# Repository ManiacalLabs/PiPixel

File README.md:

If you require support, please post to the [Maniacal Labs Google Group](https://github.com/ManiacalLabs/PiPixel/blob/master/Usage.md#data-output-options).

# Maniacal Labs PiPixel

The PiPixel provides simplified hookup of digital LED strips to the Raspberry Pi family of single board computers. It uses the standard Pi "HAT" form-factor to provide two easy power input options, and data output of the SPI port as well as GPIO 18 and 13 (used for WS2812), along with built-in voltage level shifting to keep your LED strips happy being connected to the 3.3V Pi. No longer will you have a rats-nest of wires and power between your Pi and your LEDs. Slap on the PiPixel, connect power, connect LEDs, and go!

# What's In The Bag

Your PiPixel is a user assembled kit which only requires basic soldering skills and comes with the following components:

- PiPixel PCB
- Female 2x20 Header for connection to Pi
- 2.1 / 5.5 mm barrel jack for power input option #1
- 5mm pitch dual screw terminal for power input option #2
- 74AHCT125 Level Shifter
- 4 pin screw terminal for data/power output
- 2x3 pin header and jumper for data line selection

# Where To Get Optional Headers

We ship the PiPixel with a standard 2x20 Female header as that's what most users are likely to use. But it supports a few other options which we don't currently provide. See the list below for links of where to buy those, should you need them.

- [Extra Tall Female Header](https://www.sparkfun.com/products/14017)
- [Male Header](https://www.sparkfun.com/products/14275)
- [Stacking Header](https://www.adafruit.com/product/1979)
- [Ribbon Cable](https://www.sparkfun.com/products/13028)

# Assembly

Check out the full [Assembly doc](Assembly.md)

# Usage

For all the details on using your PiPixel, check out the [Usage doc](Usage.md)

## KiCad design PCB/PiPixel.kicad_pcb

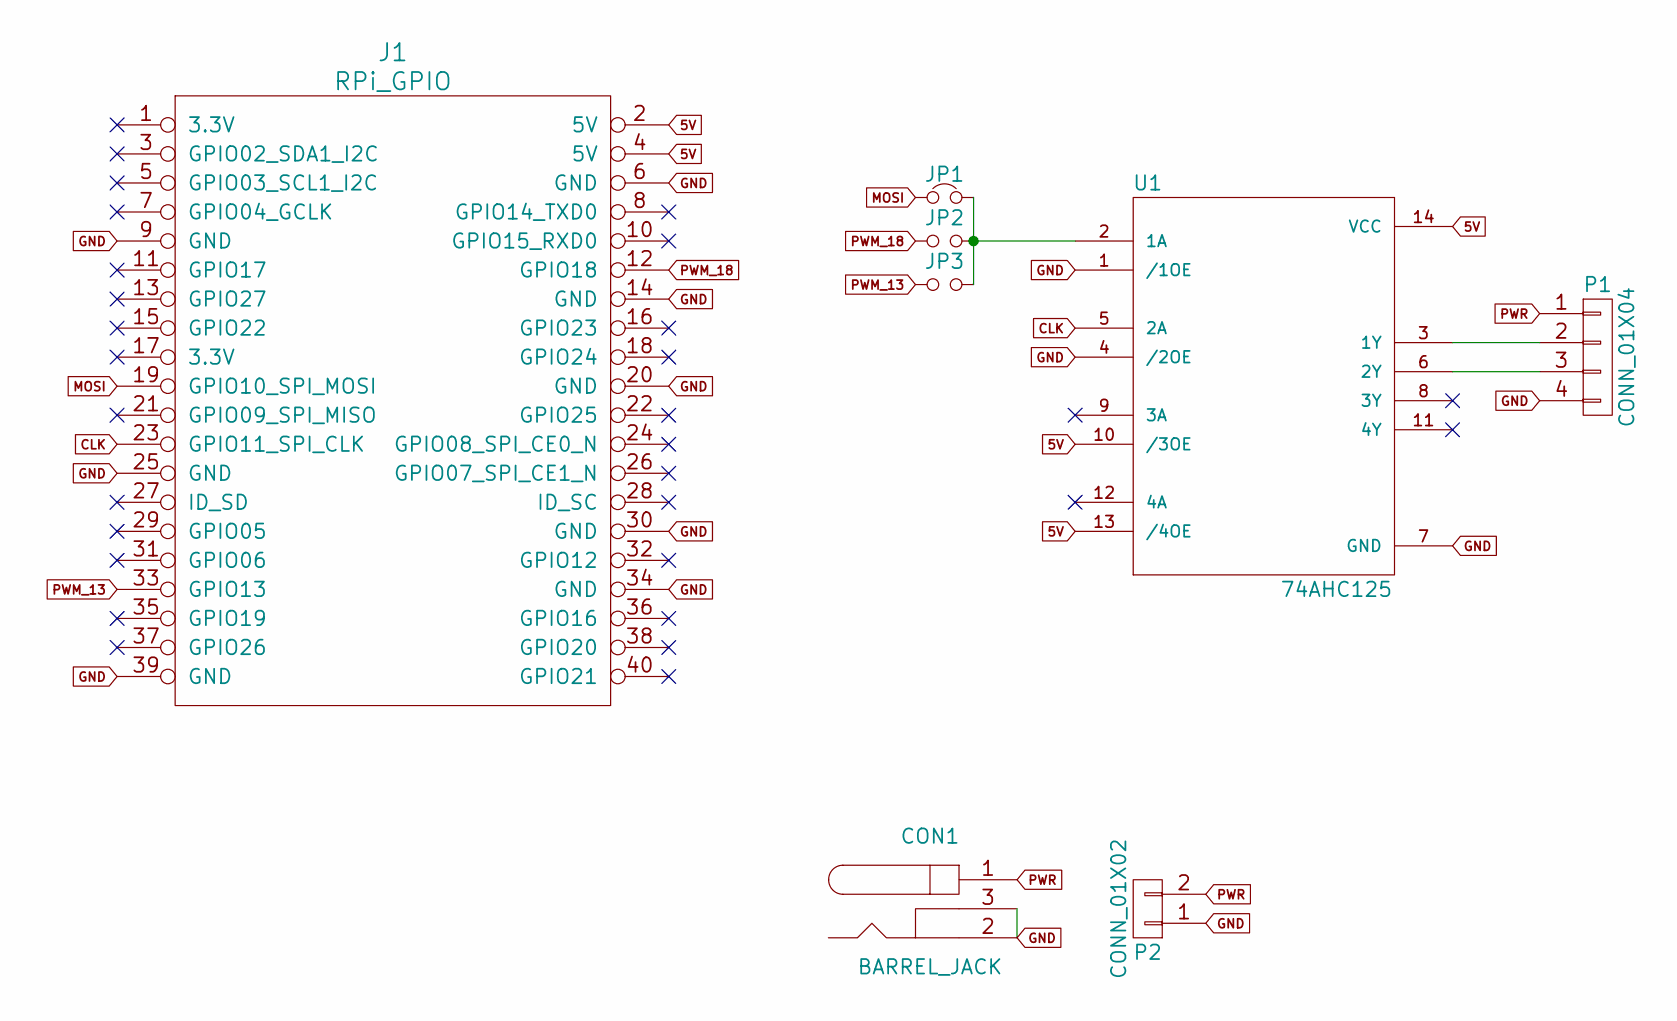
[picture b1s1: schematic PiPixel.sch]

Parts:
CON1: BARREL_JACK; ML_BARREL_JACK_ROUND_PADS_SHORT
J1: RPi_GPIO; Pin_Header_Straight_2x20
JP1: Jumper_NC_Small; Socket_Strip_Straight_1x02
JP2, JP3: Jumper_NO_Small; Socket_Strip_Straight_1x02
P1: CONN_01X04; mpt_0,5%2f4-2,54
P2: CONN_01X02; mkds_1,5-2
U1: 74AHC125; DIP-14_W7.62mm_LongPads

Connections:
5V: J1.2 (5V), J1.4 (5V), U1.10 (/3OE), U1.13 (/4OE), U1.14 (VCC)
CLK: J1.23 (GPIO11_SPI_CLK), U1.5 (2A)
GND: CON1.2, CON1.3, J1.6 (GND), J1.9 (GND), J1.14 (GND), J1.20 (GND), J1.25 (GND), J1.30 (GND), J1.34 (GND), J1.39 (GND), P1.4, P2.1, U1.1 (/1OE), U1.4 (/2OE), U1.7 (GND)
MOSI: J1.19 (GPIO10_SPI_MOSI), JP1.1
unnamed: JP1.2, JP2.2, JP3.2, U1.2 (1A)
unnamed: P1.2, U1.3 (1Y)
unnamed: P1.3, U1.6 (2Y)
PWM_13: J1.33 (GPIO13), JP3.1
PWM_18: J1.12 (GPIO18), JP2.1
PWR: CON1.1, P1.1, P2.2

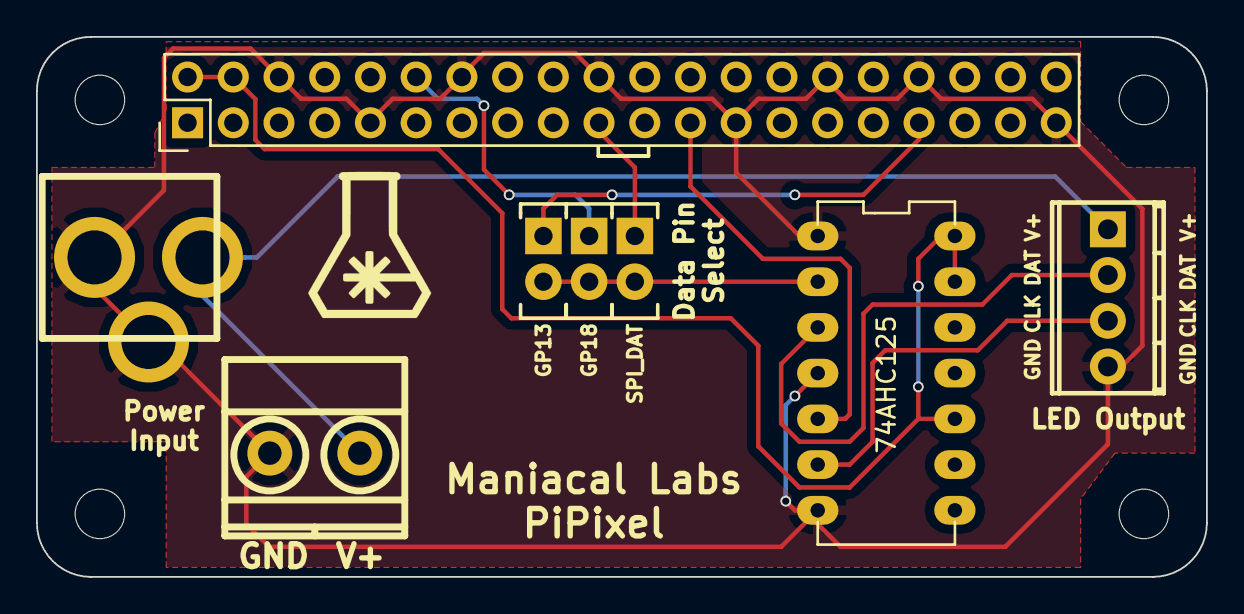
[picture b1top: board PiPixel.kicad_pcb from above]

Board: 2 copper layers, 65.0 x 30.0 mm, 8 parts (0 on the bottom side), 10 nets.

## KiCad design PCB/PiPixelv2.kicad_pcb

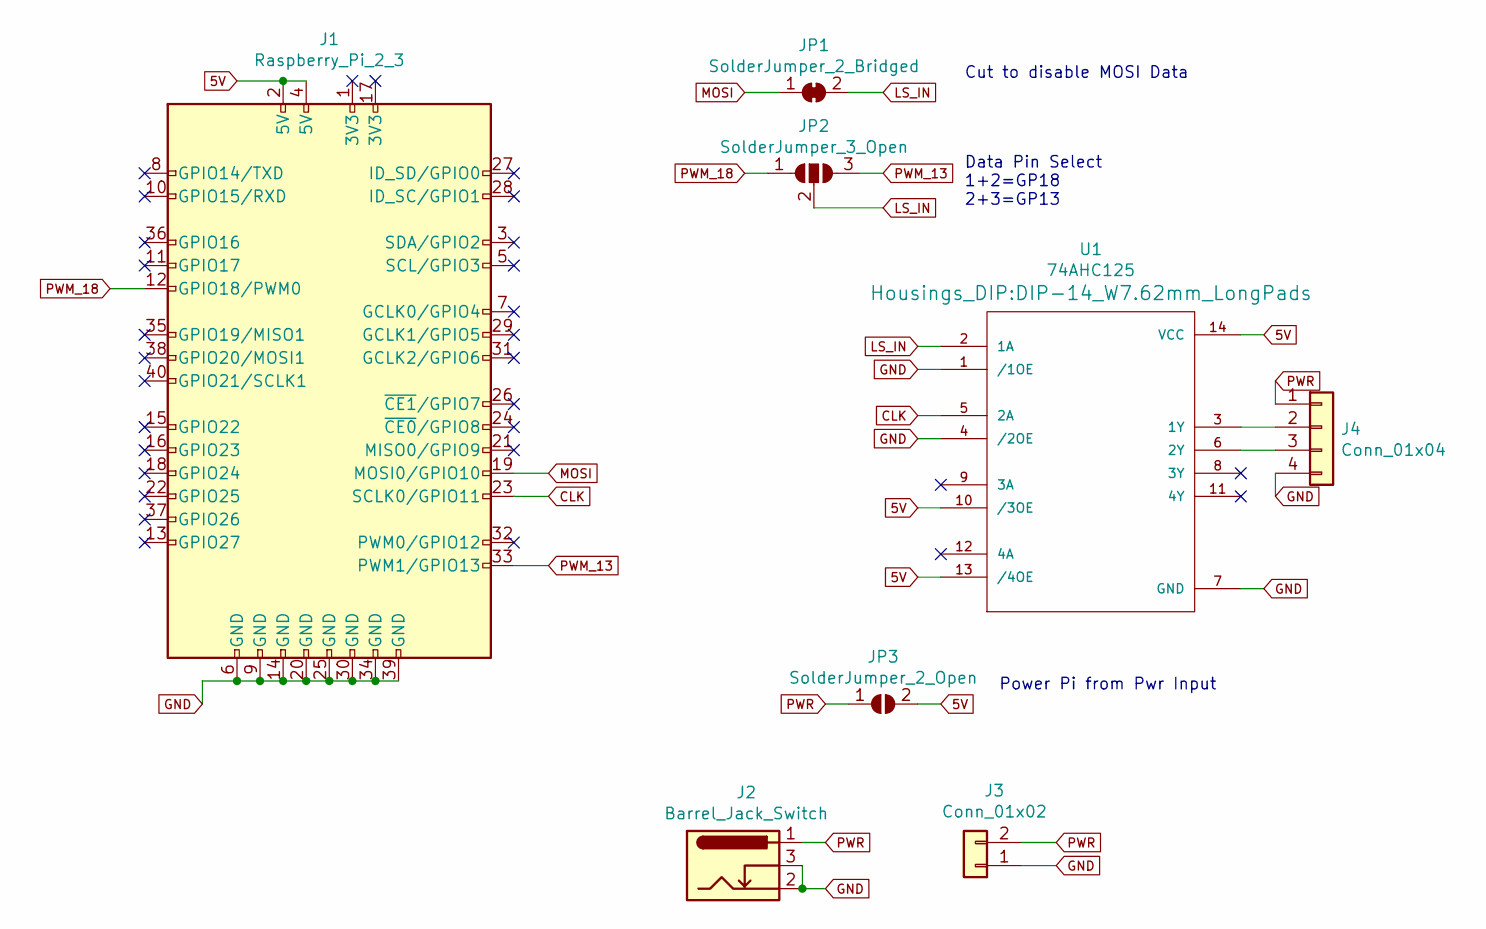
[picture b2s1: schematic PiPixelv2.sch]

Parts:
J1: Raspberry_Pi_2_3; Pin_Header_Straight_2x20_Pitch2.54mm
J2: Barrel_Jack_Switch; ML_BARREL_JACK_ROUND_PADS_SHORT
J3: Conn_01x02; mkds_1,5-2
J4: Conn_01x04; mpt_0,5%2f4-2,54
JP1: SolderJumper_2_Bridged; SolderJumper-2_P1.3mm_Bridged_Pad1.0x1.5mm
JP2: SolderJumper_3_Open; SolderJumper-3_P1.3mm_Open_Pad1.0x1.5mm_NumberLabels
JP3: SolderJumper_2_Open; SolderJumper-2_P1.3mm_Open_Pad1.0x1.5mm
U1: 74AHC125; DIP-14_W7.62mm_LongPads

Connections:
5V: J1.2 (5V), J1.4 (5V), JP3.2 (B), U1.10 (/3OE), U1.13 (/4OE), U1.14 (VCC)
CLK: J1.23 (SCLK0/GPIO11), U1.5 (2A)
GND: J1.6 (GND), J1.9 (GND), J1.14 (GND), J1.20 (GND), J1.25 (GND), J1.30 (GND), J1.34 (GND), J1.39 (GND), J2.2, J2.3, J3.1, J4.4, U1.1 (/1OE), U1.4 (/2OE), U1.7 (GND)
LS_IN: JP1.2 (B), JP2.2 (C), U1.2 (1A)
MOSI: J1.19 (MOSI0/GPIO10), JP1.1 (A)
unnamed: J4.2, U1.3 (1Y)
unnamed: J4.3, U1.6 (2Y)
PWM_13: J1.33 (PWM1/GPIO13), JP2.3 (B)
PWM_18: J1.12 (GPIO18/PWM0), JP2.1 (A)
PWR: J2.1, J3.2, J4.1, JP3.1 (A)

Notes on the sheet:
Cut to disable MOSI Data
Data Pin Select 1+2=GP18 2+3=GP13
Power Pi from Pwr Input

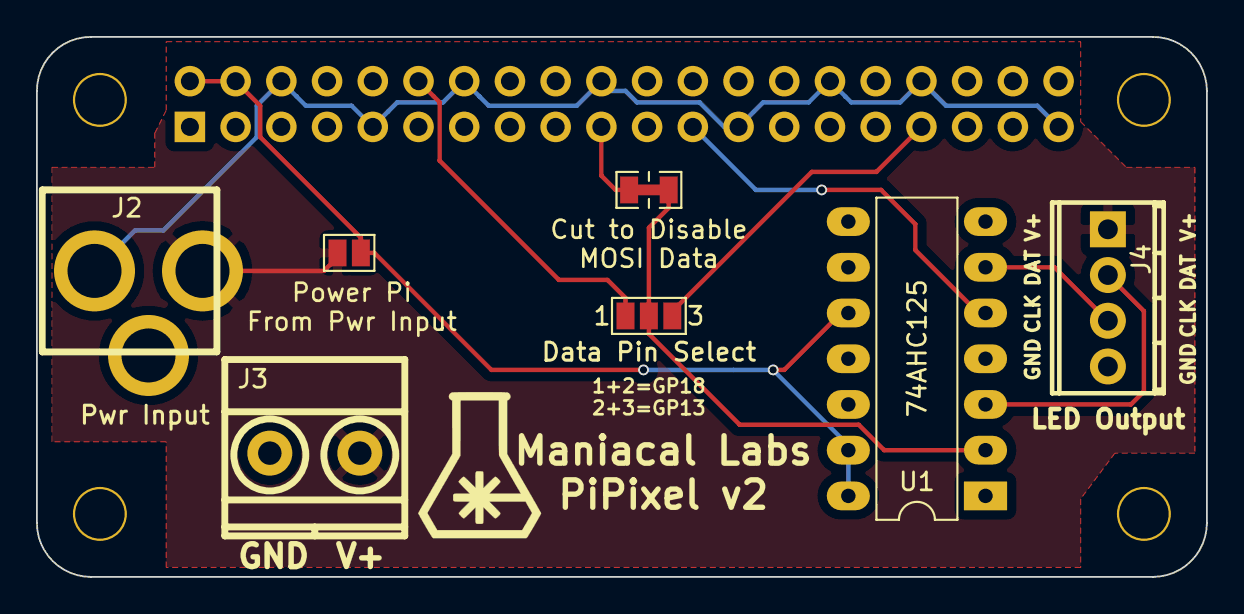
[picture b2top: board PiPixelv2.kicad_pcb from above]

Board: 2 copper layers, 65.0 x 30.0 mm, 12 parts (0 on the bottom side), 10 nets.

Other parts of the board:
H1, H1#2, H1#3, H1#4: 3mm_Mounting_Hole; NPTH_3mm_ID

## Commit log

2017-06-18 Full layout
2017-07-02 fixed GPIO mappings
2017-07-20 Updating gerbers
2017-07-20 Added mask gerbers
2017-08-12 Re-organize everything
2017-08-12 fix after merge
2017-08-12 Assembly doc
2017-08-12 updated docs
2017-08-12 added video to usage
2017-08-12 fix typo
2017-08-13 updating youtube url
2017-08-13 Adding header options to README
2019-07-28 Initial Commit of PiPixelv2
2019-07-28 Further PCB changes, library adds
2019-07-28 v2 PCB layout, traces complete.
2019-07-28 Made GND connections to top row of pins on Pi header, DRC Pass
2019-08-20 Updated FSilk with RefDes for MFG
2019-08-20 Generated gerber files for submission to Seeed for quote
2019-08-22 Modified Pi Header to show on BSilk
2019-08-22 Committing BOM file for PiPixelV2
2019-08-28 adding CAD models for v1
2020-01-01 Changed v2 design to TH Level Shifter
